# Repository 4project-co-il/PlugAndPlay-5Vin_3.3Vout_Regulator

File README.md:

# PlugAndPlay: Regulator module for 5V IN, output: 3.3V/0.6A
This is the repository with the files for PlugAndPlay regulator module that accepts 5V input and output 3.3V/0.6A.
This is the default regulator supplied with the Plug-n-Play SAMD21 Dev board.

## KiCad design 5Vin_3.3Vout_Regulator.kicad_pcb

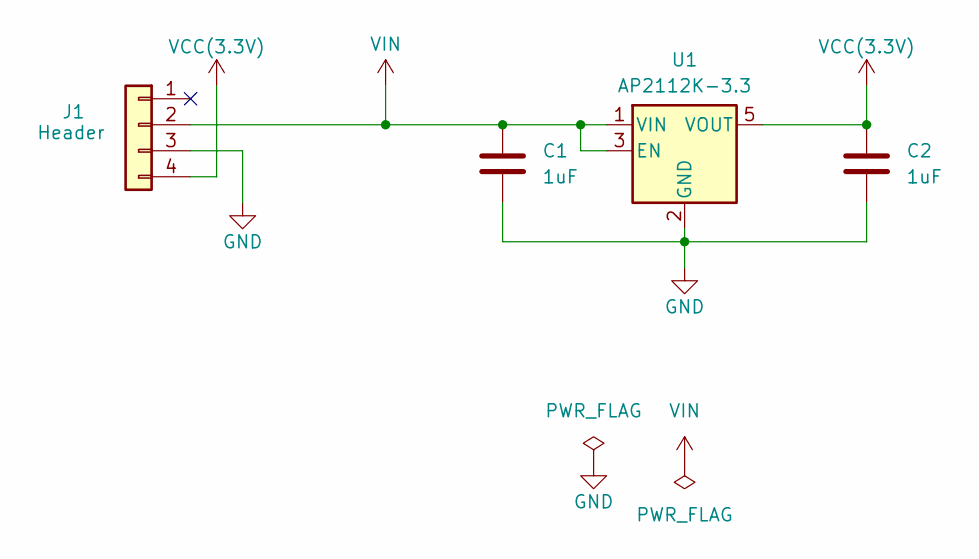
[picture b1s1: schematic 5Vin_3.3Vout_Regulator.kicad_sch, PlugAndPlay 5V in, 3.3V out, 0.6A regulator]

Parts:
C1, C2: 1uF; C_0603_1608Metric; MPN C1592
J1: PinHeader_1x04_P2.54mm_Vertical_SMD_Pin1Left; PinSocket_1x04_P2.54mm_Vertical_SMD_Pin1Left; MPN C780062
U1: AP2112K-3.3; SOT-23-5; MPN C51118

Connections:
GND: C1.2, C2.2, J1.3, U1.2 (GND)
VCC(3.3V): C2.1, J1.4, U1.5 (VOUT)
VIN: C1.1, J1.2, U1.1 (VIN), U1.3 (EN)

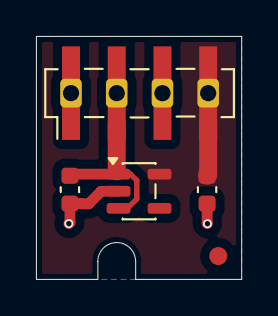
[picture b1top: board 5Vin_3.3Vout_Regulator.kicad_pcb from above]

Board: 2 copper layers, 11.4 x 13.5 mm, 4 parts (0 on the bottom side), 3 nets.
